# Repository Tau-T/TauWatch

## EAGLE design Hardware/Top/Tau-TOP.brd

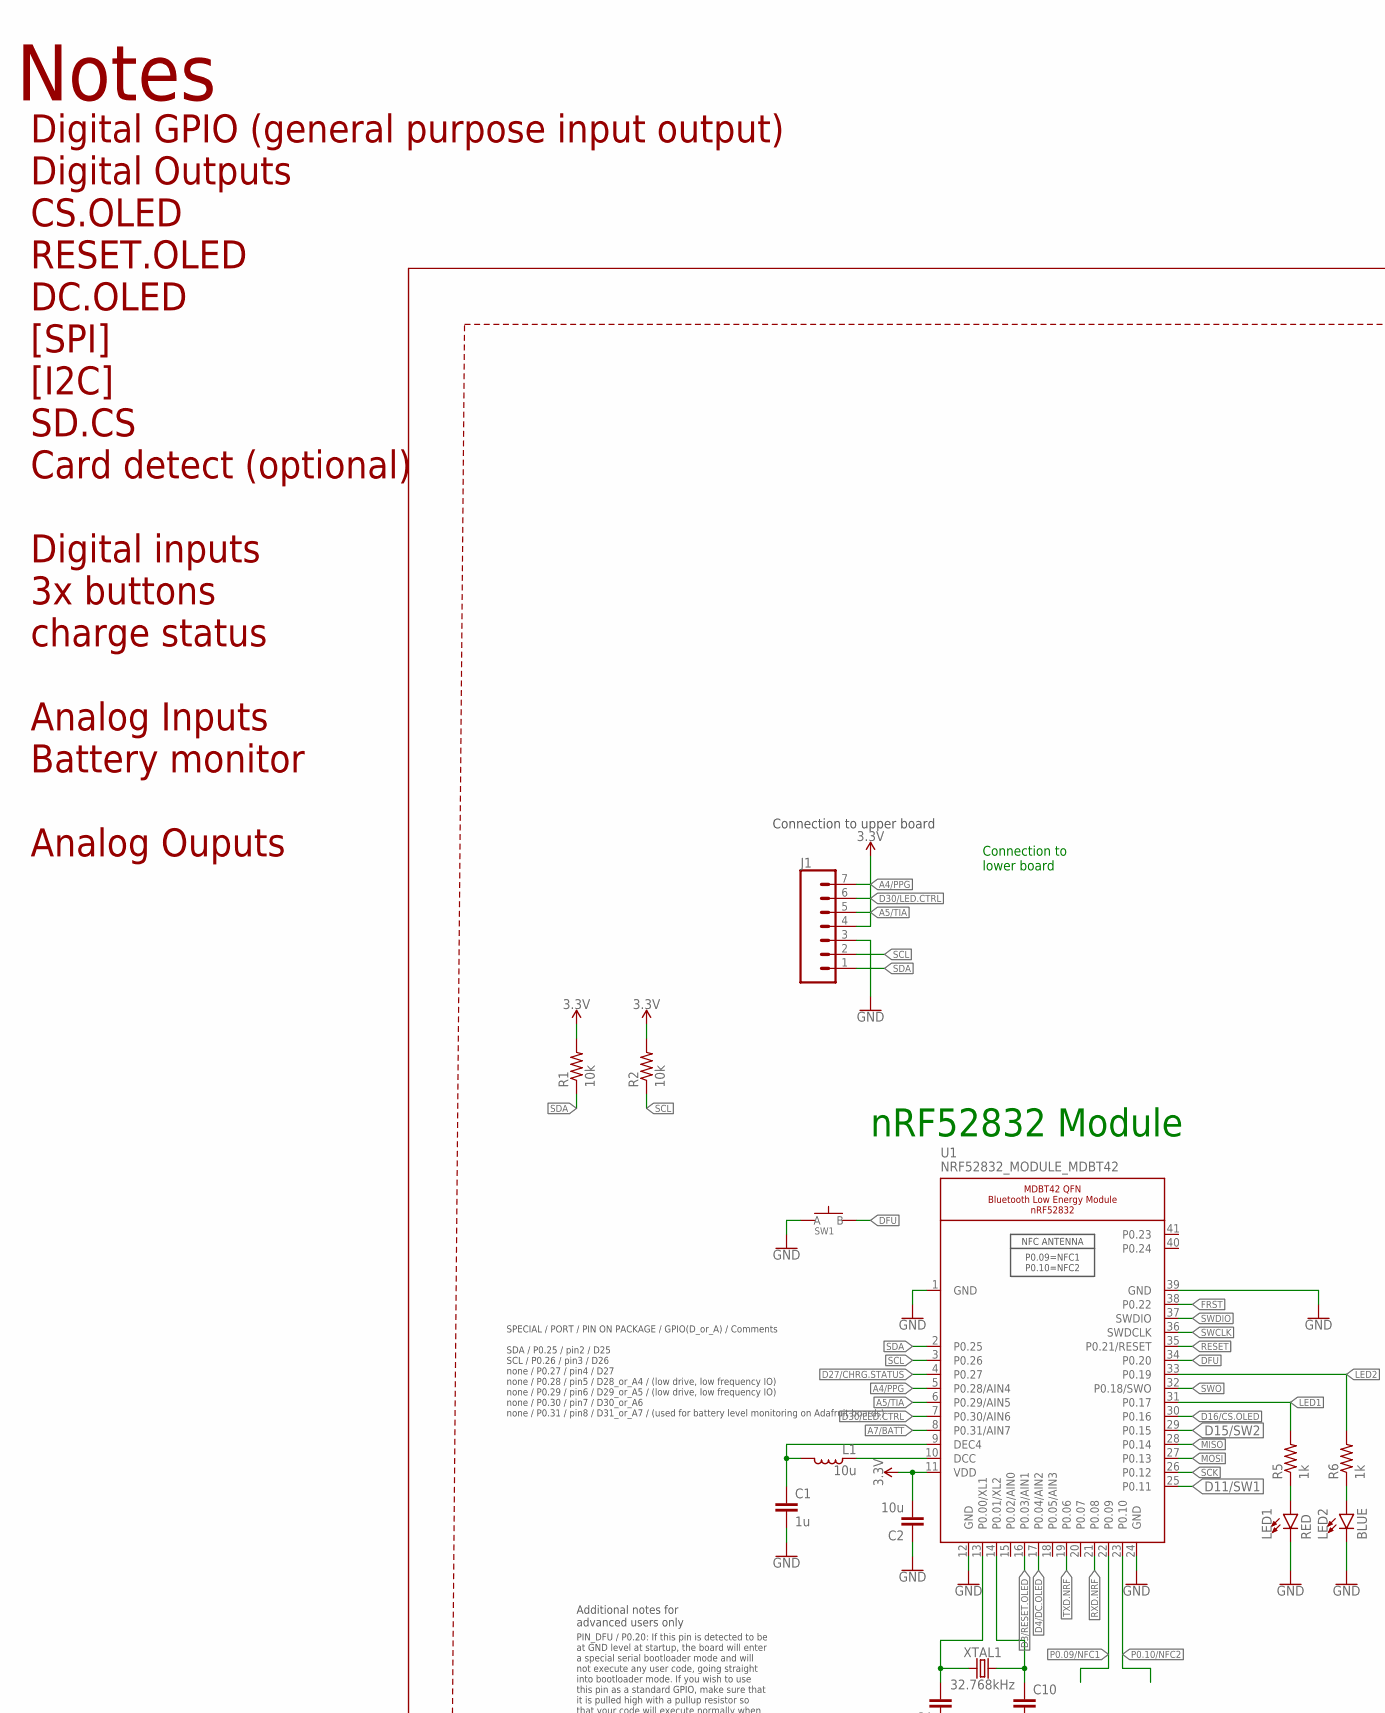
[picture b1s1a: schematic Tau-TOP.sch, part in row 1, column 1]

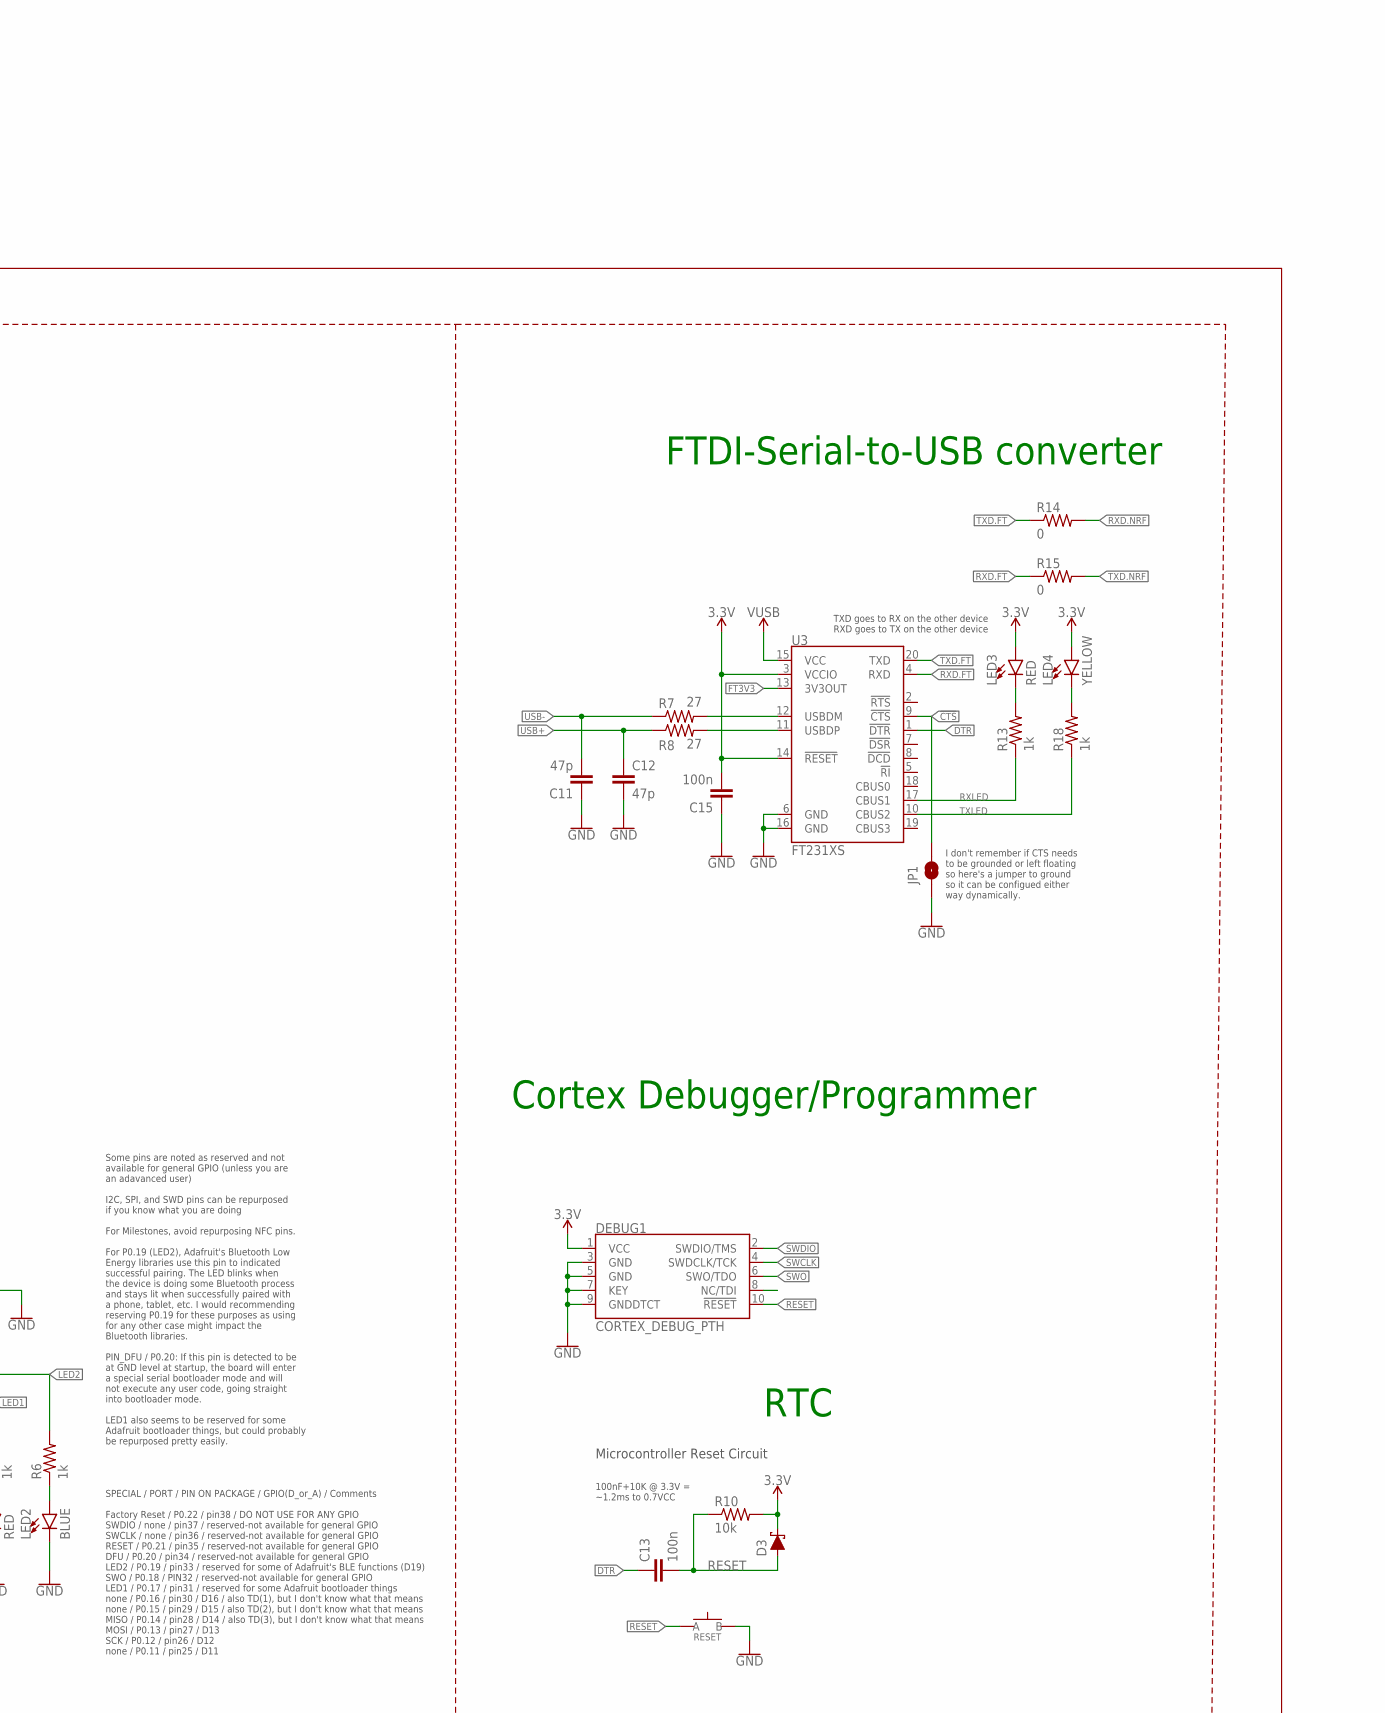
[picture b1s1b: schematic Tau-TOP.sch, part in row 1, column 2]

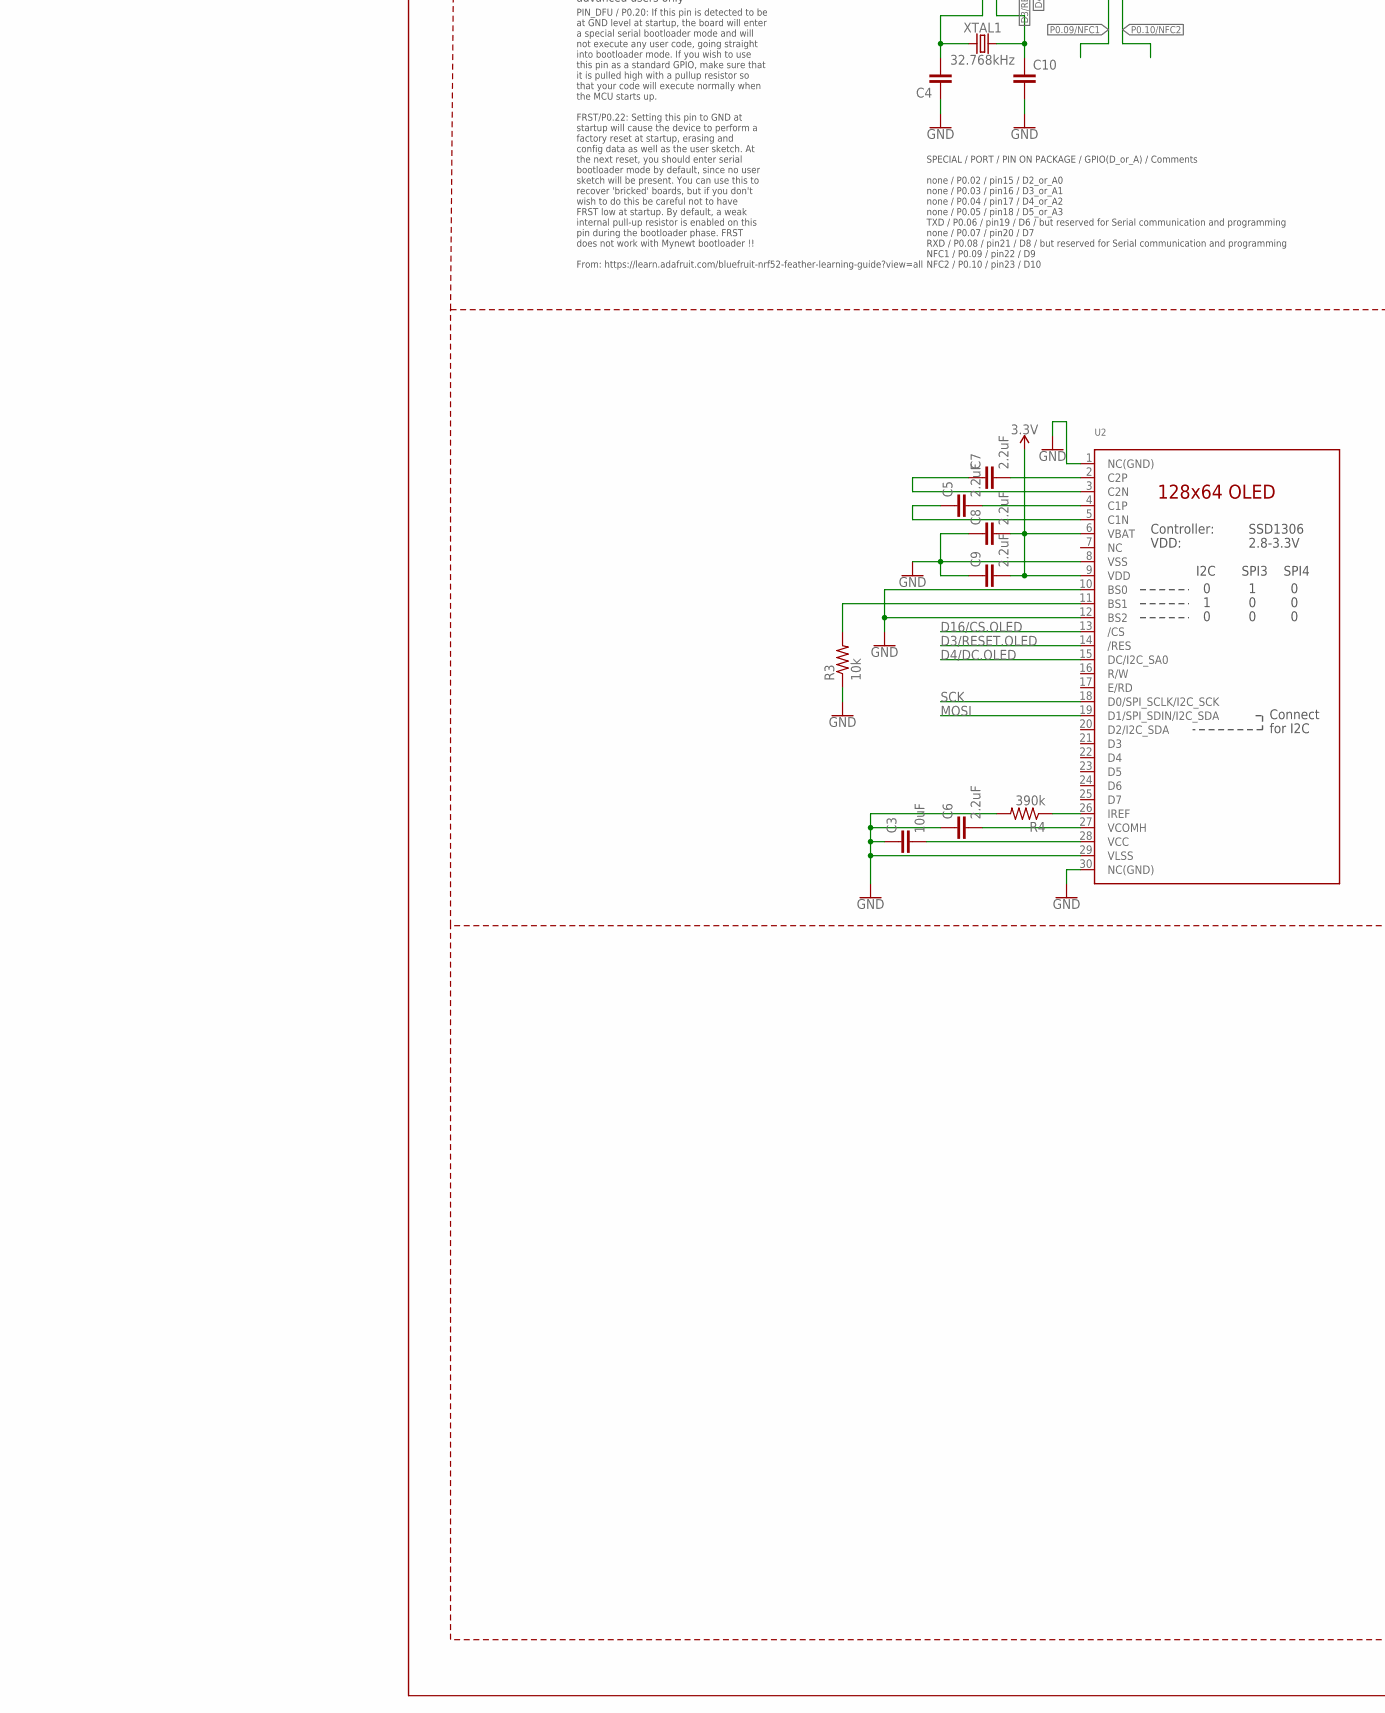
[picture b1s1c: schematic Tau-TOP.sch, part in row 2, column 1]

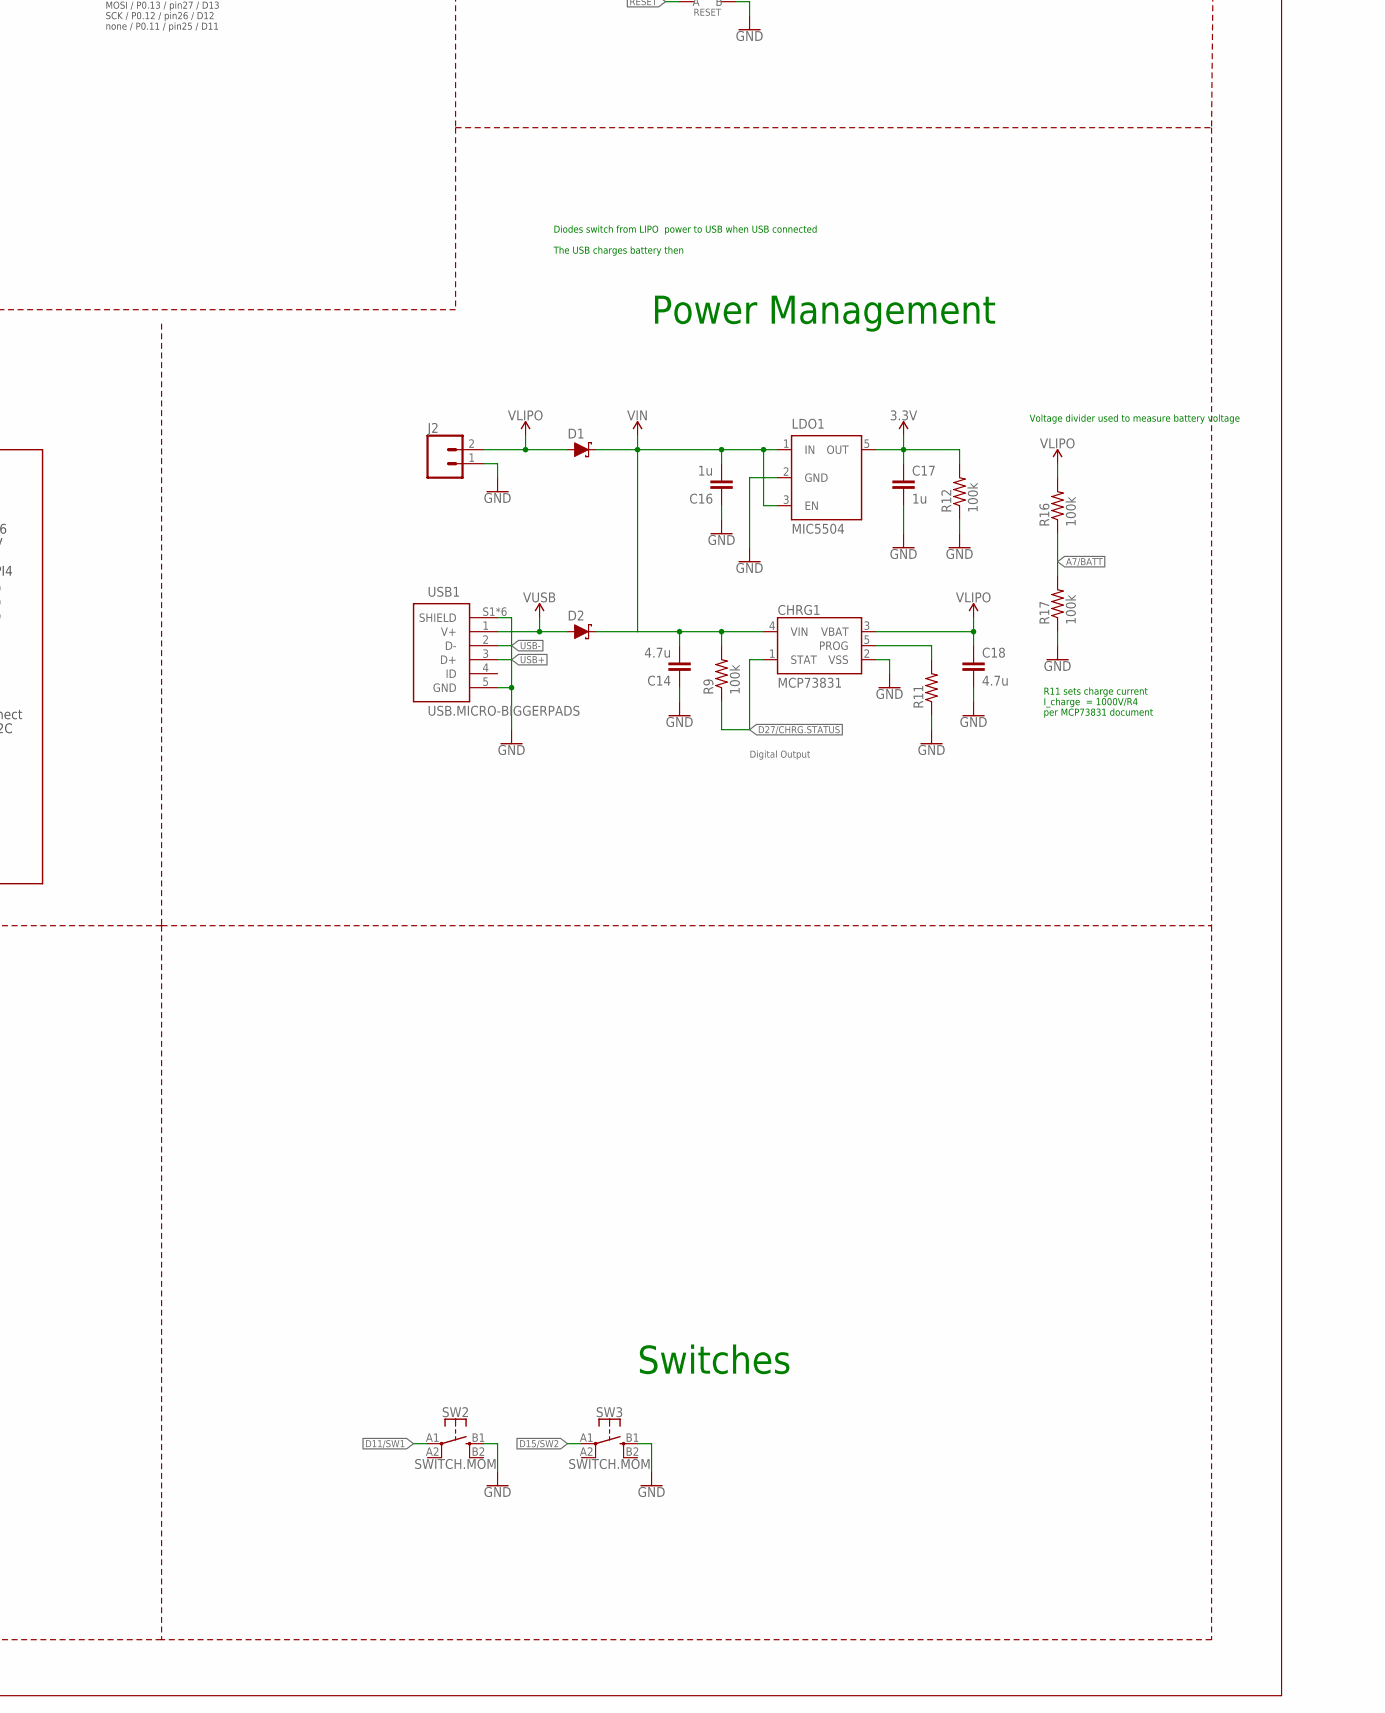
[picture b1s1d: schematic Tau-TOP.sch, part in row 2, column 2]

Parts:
C1, C16, C17: 1u; C0603
C2: 10u; C0805
C3: 10uF; C0603
C4, C10: CAPACITOR0603; C0603
C5, C6, C7, C8, C9: 2.2uF; C0402
C11, C12: 47p; C0603
C13, C15: 100n; C0603
C14, C18: 4.7u; C0603
CHRG1: MCP73831; SOT23-5
D1, D2, D3: SCHOTTKY-USC; USC
DEBUG1: CORTEX_DEBUG_PTH; 2X5-PTH-1.27MM
J1: CONN_07-1.27MM; 1X07_1.27MM
J2: CONN_02; 1X02
JP1: JUMPER-SMT_2_NO_SILK; SMT-JUMPER_2_NO_SILK
L1: 10u; L0603
LDO1: MIC5504; SOT23-5
LED1, LED3: RED; LED-0603
LED2: BLUE; LED-0603
LED4: YELLOW; LED-0603
R1, R2, R3, R10: 10k; R0603
R4: 390k; R0603
R5, R6, R13, R18: 1k; R0603
R7, R8: 27; R0603
R9, R12, R16, R17: 100k; R0603
R11: RESISTOR0603; R0603
R14, R15: 0; R0603
RESET: SPST-PTS830GG140-COPY.1-3; BUTTON-GULLWING
SW1: SPST-PTS830GG140-COPY.1-3; BUTTON-GULLWING
SW2, SW3: SWITCH.MOM; TACTILE_SWITCH_SMD_6.2MM_TALL
U1: NRF52832_MODULE_MDBT42; BLE_MODULE_RAYTAC_MDBT42
U2: DISP_OLED_UG-2864HSWEG01-NO-WRAPAROUND; UG-2864HSWEG01_0.96IN_NO-WRAPAROUND
U3: FT231XS; SSOP20_L
USB1: USB.MICRO-BIGGERPADS; USB-MICRO-01.BIGGERPADS
XTAL1: 32.768kHz; 2-SMD.NOLEAD.2.0MMTO1.2MM

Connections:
3.3V: C2.2, C8.2, C9.2, C15.2, C17.1, D3.- (C), DEBUG1.1 (VCC), J1.4, LDO1.5 (OUT), LED3.A, LED4.A, R1.2, R2.2, R10.2, R12.2, U1.11 (VDD), U2.6 (VBAT), U2.9 (VDD), U3.3 (VCCIO), U3.14 (!RESET)
!CTS: JP1.2, U3.9 (!CTS)
A4/PPG: J1.7, U1.5 (P0.28/AIN4)
A5/TIA: J1.5, U1.6 (P0.29/AIN5)
A7/BATT: R16.1, R17.2, U1.8 (P0.31/AIN7)
D3/RESET.OLED: U1.16 (P0.03/AIN1), U2.14 (/RES)
D4/DC.OLED: U1.17 (P0.04/AIN2), U2.15 (DC/I2C_SA0)
D11/SW1: SW2.A1 (1), U1.25 (P0.11)
D15/SW2: SW3.A1 (1), U1.29 (P0.15)
D16/CS.OLED: U1.30 (P0.16), U2.13 (/CS)
D27/CHRG.STATUS: CHRG1.1 (STAT), R9.1, U1.4 (P0.27)
D30/LED.CTRL: J1.6, U1.7 (P0.30/AIN6)
DFU: SW1.3 (B), U1.34 (P0.20)
DTR: C13.1, U3.1 (!DTR)
FRST: U1.38 (P0.22)
FT3V3: U3.13 (3V3OUT)
GND: C1.2, C2.1, C3.1, C4.1, C6.1, C8.1, C9.1, C10.2, C11.1, C12.2, C14.1, C15.1, C16.1, C17.2, C18.2, CHRG1.2 (VSS), DEBUG1.3 (GND), DEBUG1.5 (GND), DEBUG1.7 (KEY), DEBUG1.9 (GNDDTCT), J1.3, J2.1, JP1.1, LDO1.2 (GND), LED1.C, LED2.C, R3.1, R4.2, R11.1, R12.1, R17.1, RESET.3 (B), SW1.1 (A), SW2.B1 (3), SW3.B1 (3), U1.1 (GND), U1.12 (GND), U1.24 (GND), U1.39 (GND), U2.1 (NC(GND)), U2.8 (VSS), U2.10 (BS0), U2.12 (BS2), U2.29 (VLSS), U2.30 (NC(GND)), U3.6 (GND), U3.16 (GND), USB1.5 (GND), USB1.S1 (SHIELD), USB1.S2 (SHIELD), USB1.S3 (SHIELD), USB1.S4 (SHIELD), USB1.S5 (SHIELD), USB1.S6 (SHIELD)
LED1: R5.2, U1.31 (P0.17)
LED2: R6.2, U1.33 (P0.19)
MISO: U1.28 (P0.14)
MOSI: U1.27 (P0.13), U2.19 (D1/SPI_SDIN/I2C_SDA)
unnamed: R3.2, U2.11 (BS1)
unnamed: R4.1, U2.26 (IREF)
unnamed: C7.2, U2.2 (C2P)
unnamed: C7.1, U2.3 (C2N)
unnamed: C5.2, U2.4 (C1P)
unnamed: C5.1, U2.5 (C1N)
unnamed: C3.2, U2.28 (VCC)
unnamed: C6.2, U2.27 (VCOMH)
unnamed: CHRG1.5 (PROG), R11.2
unnamed: R7.2, U3.12 (USBDM)
unnamed: R8.2, U3.11 (USBDP)
unnamed: LED3.C, R13.2
unnamed: LED4.C, R18.2
unnamed: C4.2, U1.13 (P0.00/XL1), XTAL1.P$1 (1)
unnamed: C10.1, U1.14 (P0.01/XL2), XTAL1.P$2 (2)
unnamed: LED1.A, R5.1
unnamed: LED2.A, R6.1
unnamed: L1.1, U1.10 (DCC)
unnamed: C1.1, L1.2, U1.9 (DEC4)
P0.09/NFC1: U1.22 (P0.09)
P0.10/NFC2: U1.23 (P0.10)
RESET: C13.2, D3.+ (A), DEBUG1.10 (!RESET), R10.1, RESET.1 (A), U1.35 (P0.21/RESET)
RXD.FT: R15.1, U3.4 (RXD)
RXD.NRF: R14.2, U1.21 (P0.08)
RXLED: R13.1, U3.17 (CBUS1)
SCK: U1.26 (P0.12), U2.18 (D0/SPI_SCLK/I2C_SCK)
SCL: J1.2, R2.1, U1.3 (P0.26)
SDA: J1.1, R1.1, U1.2 (P0.25)
SWCLK: DEBUG1.4 (SWDCLK/TCK), U1.36 (SWDCLK)
SWDIO: DEBUG1.2 (SWDIO/TMS), U1.37 (SWDIO)
SWO: DEBUG1.6 (SWO/TDO), U1.32 (P0.18/SWO)
TXD.FT: R14.1, U3.20 (TXD)
TXD.NRF: R15.2, U1.19 (P0.06)
TXLED: R18.1, U3.10 (CBUS2)
USB+: C12.1, R8.1, USB1.3 (D+)
USB-: C11.2, R7.1, USB1.2 (D-)
VIN: D1.- (C), D2.- (C)
VIN1: C14.2, C16.2, CHRG1.4 (VIN), LDO1.1 (IN), LDO1.3 (EN), R9.2
VLIPO: C18.1, CHRG1.3 (VBAT), D1.+ (A), J2.2, R16.2
V_USB: D2.+ (A), U3.15 (VCC), USB1.1 (V+)

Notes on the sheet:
Microcontroller Reset Circuit
100nF+10K @ 3.3V = ~1.2ms to 0.7VCC
nRF52832 Module
Cortex Debugger/Programmer
RTC
Power Management
Switches
Digital GPIO (general purpose input output) Digital Outputs CS.OLED RESET.OLED DC.OLED [SPI] [I2C] SD.CS Card detect (optional) Digital inputs 3x buttons charge status Analog Inputs Battery monitor Analog Ouputs
TXD goes to RX on the other device RXD goes to TX on the other device
I don't remember if CTS needs to be grounded or left floating so here's a jumper to ground so it can be configued either way dynamically.
FTDI-Serial-to-USB converter
Notes
Connection to upper board
Connection to lower board
SPECIAL / PORT / PIN ON PACKAGE / GPIO(D_or_A) / Comments SDA / P0.25 / pin2 / D25 SCL / P0.26 / pin3 / D26 none / P0.27 / pin4 / D27 none / P0.28 / pin5 / D28_or_A4 / (low drive, low frequency IO) none / P0.29 / pin6 / D29_or_A5 / (low drive, low frequency IO) none / P0.30 / pin7 / D30_or_A6 none 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
SPECIAL / PORT / PIN ON PACKAGE / GPIO(D_or_A) / Comments none / P0.02 / pin15 / D2_or_A0 none / P0.03 / pin16 / D3_or_A1 none / P0.04 / pin17 / D4_or_A2 none / P0.05 / pin18 / D5_or_A3 TXD / P0.06 / pin19 / D6 / but reserved for Serial communication and programming none / P0.07 / pin20 / D7 RXD / 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
SPECIAL / PORT / PIN ON PACKAGE / GPIO(D_or_A) / Comments Factory Reset / P0.22 / pin38 / DO NOT USE FOR ANY GPIO SWDIO / none / pin37 / reserved-not available for general GPIO SWCLK / none / pin36 / reserved-not available for general GPIO RESET / P0.21 / pin35 / reserved-not available for general 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
Some pins are noted as reserved and not available for general GPIO (unless you are an adavanced user) I2C, SPI, and SWD pins can be repurposed if you know what you are doing For Milestones, avoid repurposing NFC pins. For P0.19 (LED2), Adafruit's Bluetooth Low Energy libraries use this pin to indic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
PIN_DFU / P0.20: If this pin is detected to be at GND level at startup, the board will enter a special serial bootloader mode and will not execute any user code, going straight into bootloader mode. If you wish to use this pin as a standard GPIO, make sure that it is pulled high with a pullup resis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
Additional notes for advanced users only
Digital Output
Diodes switch from LIPO power to USB when USB connected The USB charges battery then
R11 sets charge current I_charge = 1000V/R4 per MCP73831 document
Voltage divider used to measure battery voltage

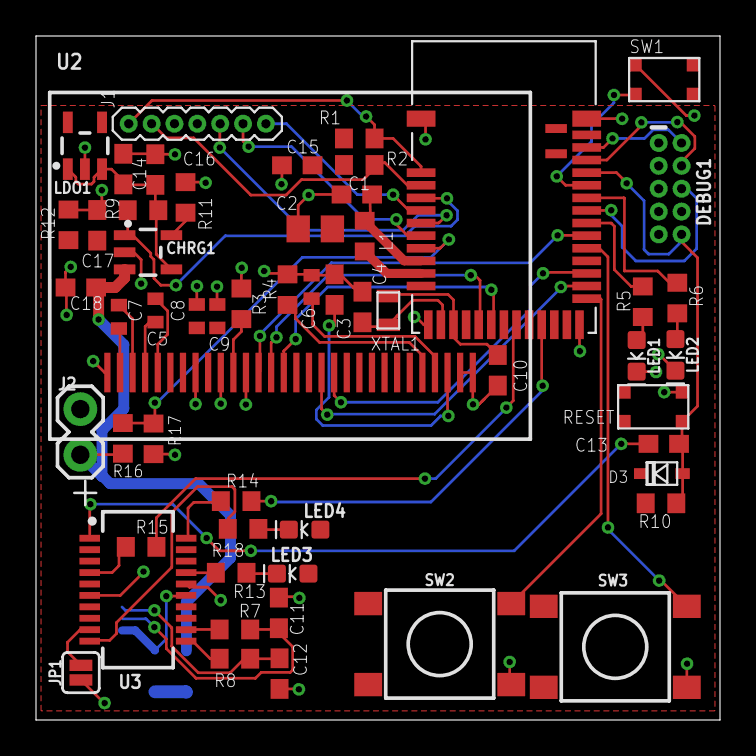
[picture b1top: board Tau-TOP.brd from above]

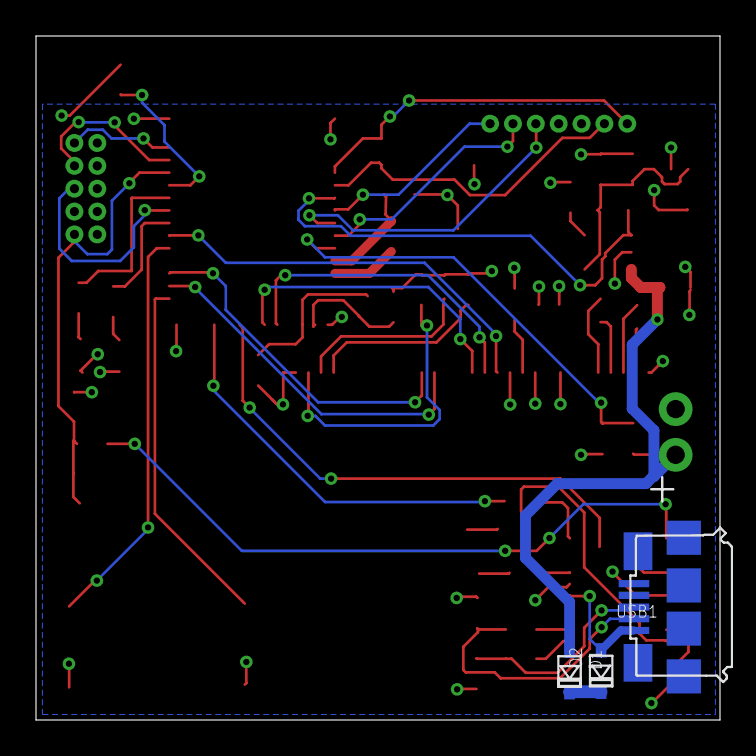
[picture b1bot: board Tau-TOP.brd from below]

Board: 2 copper layers, 38.0 x 38.0 mm, 59 parts (3 on the bottom side), 56 nets.

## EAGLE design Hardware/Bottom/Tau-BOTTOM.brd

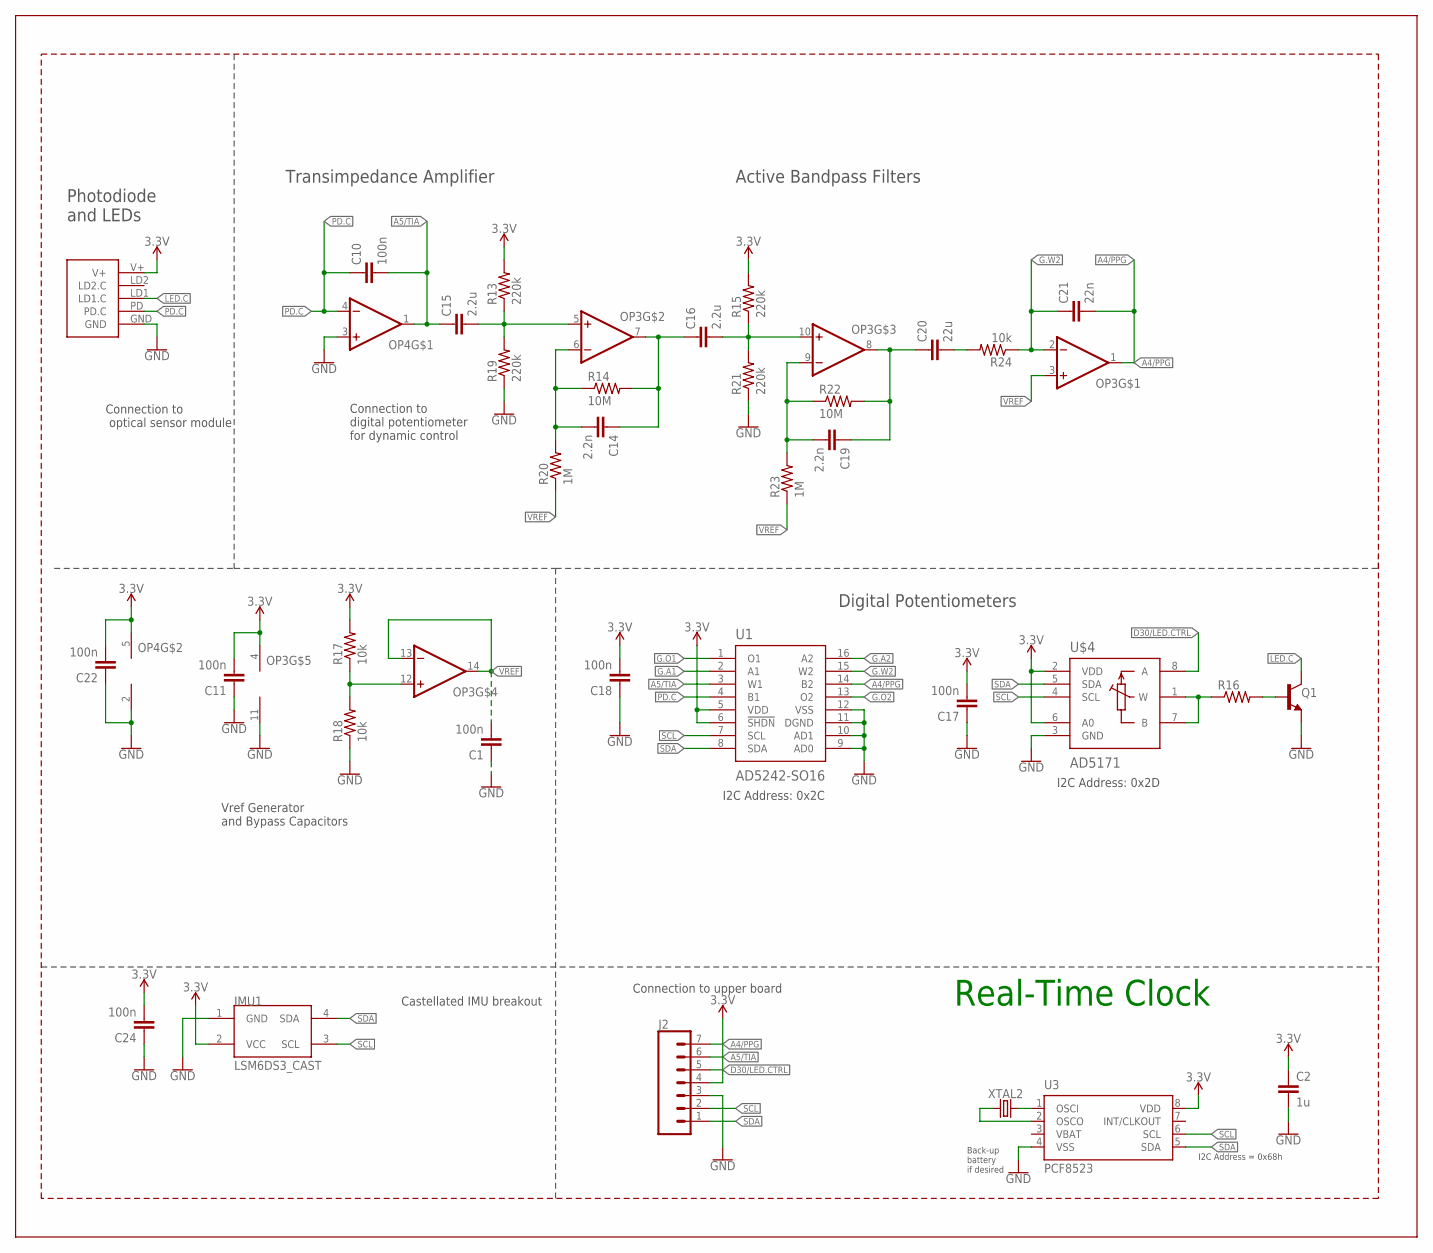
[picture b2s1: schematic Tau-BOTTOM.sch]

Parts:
C1, C10, C11, C17, C18, C22, C24: 100n; C0603
C2: 1u; C0603
C14, C19: 2.2n; C0603
C15, C16: 2.2u; C0603
C20: 22u; C0603
C21: 22n; C0603
IMU1: LSM6DS3_CAST
J2: CONN_07-1.27MM; 1X07_1.27MM
OP3: OP-QUAD-SO14; SO14
OP4: OP-SINGLEOT; SOT23-5
Q1: NPN-GENERIC; SOT23-3
R13, R15, R19, R21: 220k; R0603
R14, R22: 10M; R0603
R16: RESISTOR0603; R0603
R17, R18: 10k; R0402
R20, R23: 1M; R0603
R24: 10k; R0603
U1: AD5242-SO16; SO16
U3: PCF8523; SO8; DIGIKEY 568-5306-1-ND
U$3: PPG.MODULE.2
U$4: AD5171; SOT-23-8
XTAL2: 32.7680kHz; 2-SMD.NOLEAD.2.0MMTO1.2MM

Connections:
3.3V: C2.1, C11.2, C17.2, C18.2, C22.2, C24.2, IMU1.2 (VCC), J2.4, OP3.4 (V+), OP4.5 (V+), R13.2, R15.2, R17.2, U1.5 (VDD), U1.6 (!SHDN), U3.8 (VDD), U$3.V+, U$4.2 (VDD), U$4.6 (A0)
A4/PPG: C21.2, J2.7, OP3.1 (OUT), U1.14 (B2)
A5/TIA: C10.2, C15.1, J2.6, OP4.1 (OUT), U1.3 (W1)
D30/LED.CTRL: J2.5, U$4.8 (A)
G.A1: U1.2 (A1)
G.A2: U1.16 (A2)
G.O1: U1.1 (O1)
G.O2: U1.13 (O2)
G.W2: C21.1, OP3.2 (-IN), R24.1, U1.15 (W2)
GND: C1.1, C2.2, C11.1, C17.1, C18.1, C22.1, C24.1, IMU1.1 (GND), J2.3, OP3.11 (V-), OP4.2 (V-), OP4.3 (+IN), Q1.2 (E), R18.1, R19.1, R21.1, U1.9 (AD0), U1.10 (AD1), U1.11 (DGND), U1.12 (VSS), U3.4 (VSS), U$3.GND, U$4.3 (GND)
LED.C: Q1.3 (C), U$3.LD1 (LD1.C)
unnamed: U3.1 (OSCI), XTAL2.P$2 (2)
unnamed: Q1.1 (B), R16.2
unnamed: R16.1, U$4.1 (W), U$4.7 (B)
unnamed: OP3.12 (+IN), R17.1, R18.2
unnamed: U3.2 (OSCO), XTAL2.P$1 (1)
unnamed: C15.2, OP3.5 (+IN), R13.1, R19.2
unnamed: C14.2, OP3.6 (-IN), R14.1, R20.2
unnamed: C14.1, C16.1, OP3.7 (OUT), R14.2
unnamed: C16.2, OP3.10 (+IN), R15.1, R21.2
unnamed: C19.2, OP3.9 (-IN), R22.1, R23.2
unnamed: C19.1, C20.1, OP3.8 (OUT), R22.2
unnamed: C20.2, R24.2
PD.C: C10.1, OP4.4 (-IN), U1.4 (B1), U$3.PD (PD.C)
SCL: IMU1.3 (SCL), J2.2, U1.7 (SCL), U3.6 (SCL), U$4.4 (SCL)
SDA: IMU1.4 (SDA), J2.1, U1.8 (SDA), U3.5 (SDA), U$4.5 (SDA)
VBAT: U3.3 (VBAT)
VREF: C1.2, OP3.3 (+IN), OP3.13 (-IN), OP3.14 (OUT), R20.1, R23.1

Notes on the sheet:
Photodiode and LEDs
Active Bandpass Filters
Digital Potentiometers
Transimpedance Amplifier
I2C Address: 0x2C
I2C Address: 0x2D
Connection to digital potentiometer for dynamic control
Connection to optical sensor module
Connection to upper board
Castellated IMU breakout
Vref Generator and Bypass Capacitors
Real-Time Clock
I2C Address = 0x68h
Back-up battery if desired

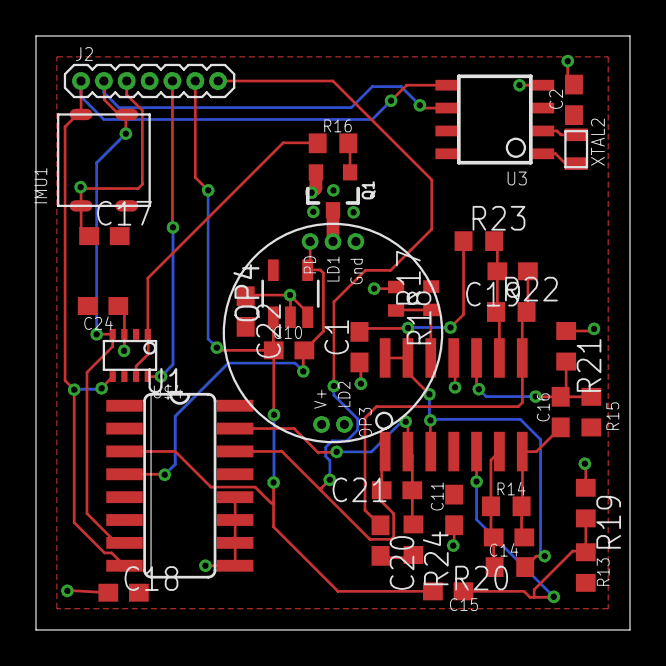
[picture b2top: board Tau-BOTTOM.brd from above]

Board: 2 copper layers, 33.0 x 33.0 mm, 36 parts (0 on the bottom side), 23 nets.

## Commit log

2020-05-28 Uploded Tau.docx
2020-06-02 Tau.docx has been committed
2020-06-04 Committed the Firmware and Hardware folders of Tau
2020-06-04 commit gitignore
2020-06-04 Changes committed to the TOP board
2020-06-04 Changes committed to top and bottom boards
2020-06-11 Changes committed to the top and bottom board. Connections between the two have been noted as well
2020-06-11 Changes committed to top and bottom board
2020-06-11 Bottom board nearly routed
2020-06-11 More routing changes to bottom board
2020-06-12 Removed extra .b and .s files
2020-06-18 Changes made to top and bottom board
2020-07-02 Changes made to Top board and arduino files
2020-07-09 Finished Bottom and Top boards' first version
2020-07-31 changes to bottom board
